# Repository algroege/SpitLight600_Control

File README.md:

// UART Communication 
// Frame Layout:
// <(SingleShot),(Shot),(PumpDelay),(PulseDivider),(DoublePulseDelay),(HV1),(HV2)>
// Example:
// <0,0,215,20,150,4.5,4.5>

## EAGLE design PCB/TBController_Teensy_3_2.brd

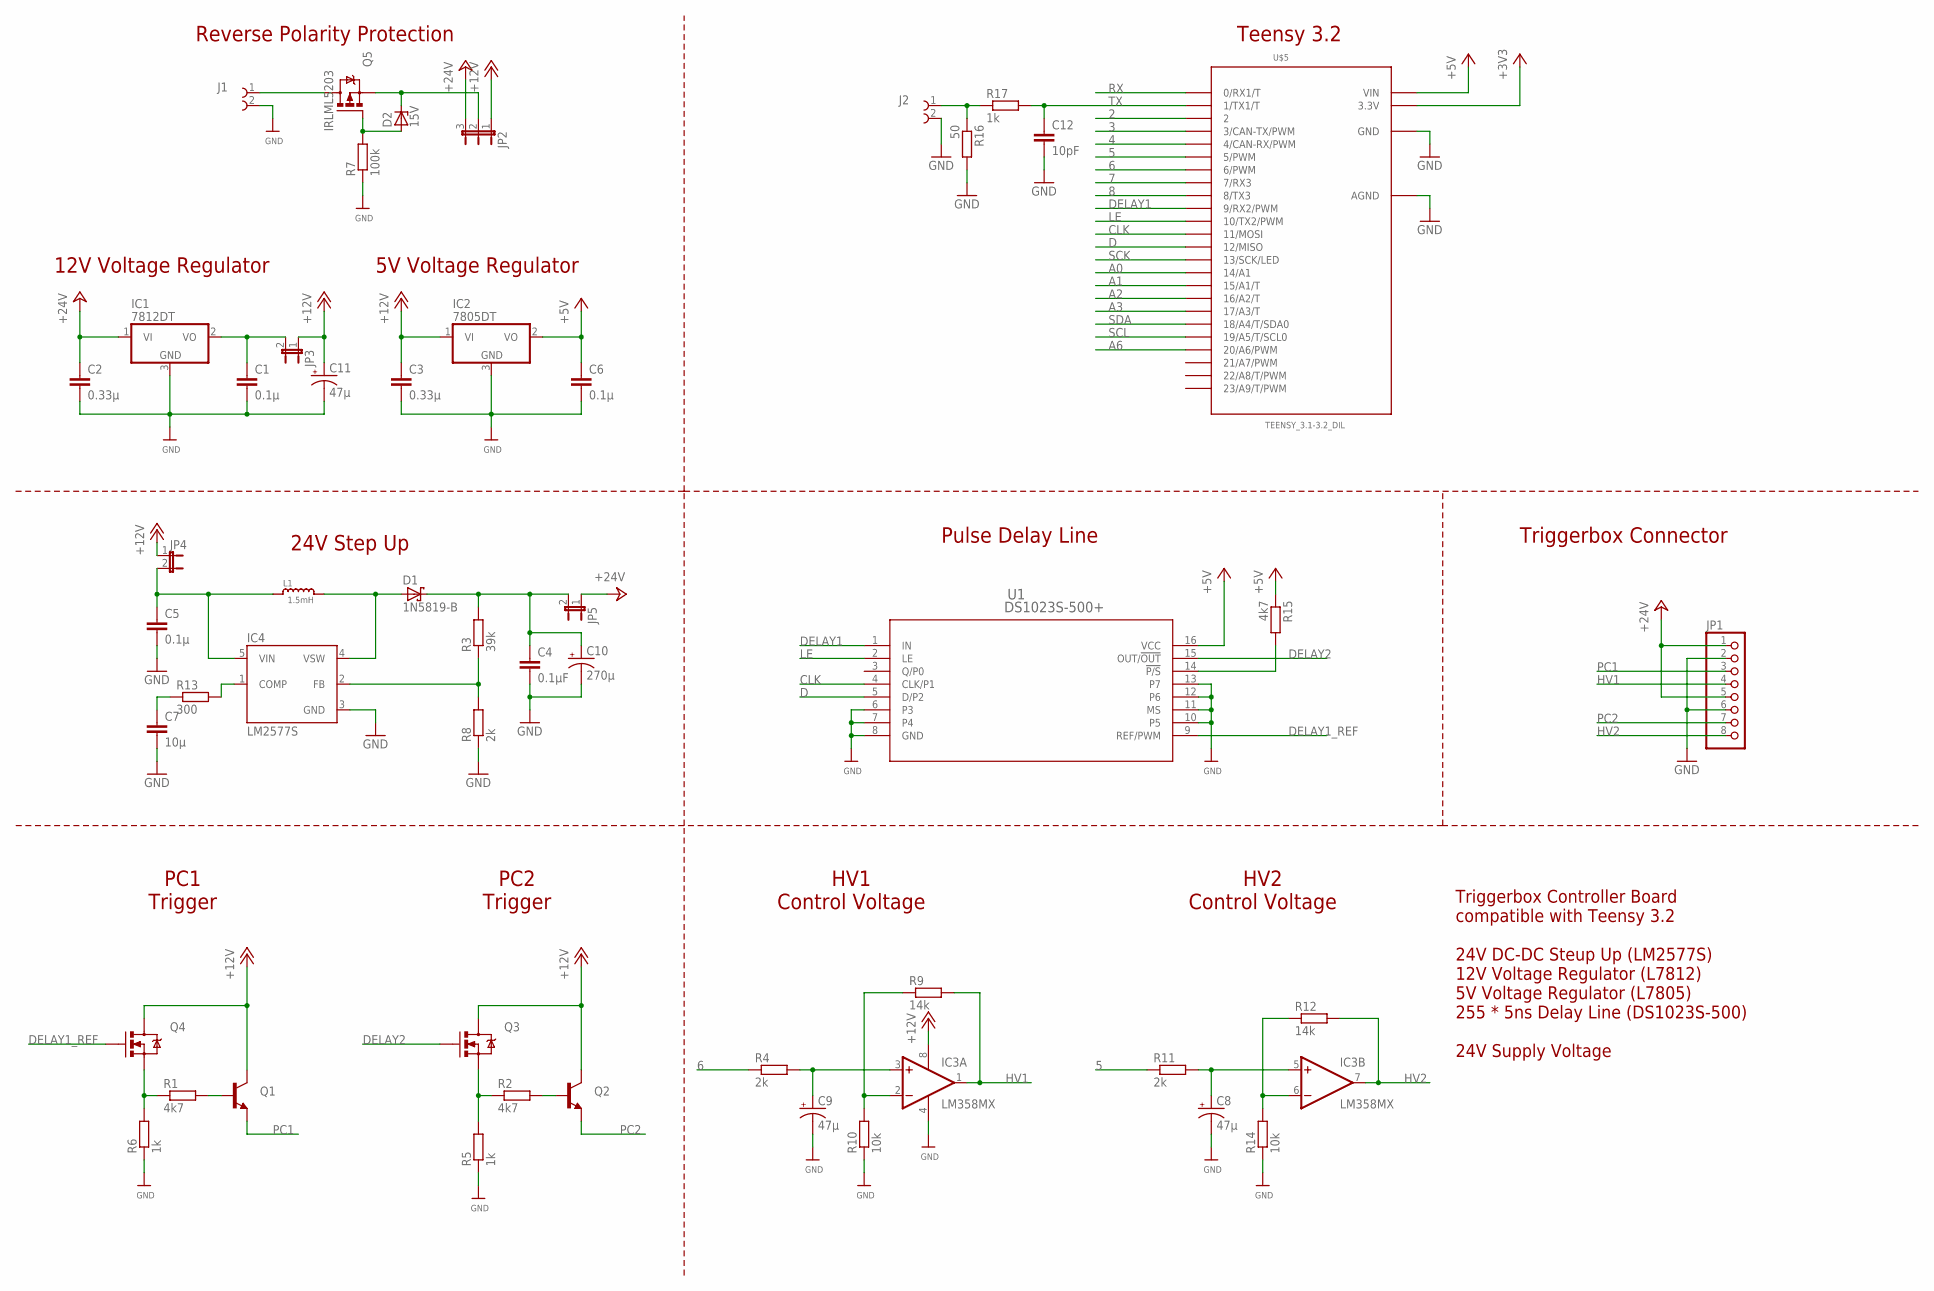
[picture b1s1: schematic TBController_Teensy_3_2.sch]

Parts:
C1, C5, C6: 0.1µ; C0805K
C2, C3: 0.33µ; C0805K
C4: 0.1µF; C0805K
C7: 10µ; C0805K
C8, C9, C11: 47µ; CPOL-RADIAL-100UF-25V
C10: 270µ; CPOL-RADIAL-100UF-25V
C12: 10pF; C0805K
D1: 1N5819-B; DO41-7.6
D2: 15V; SOT23
IC1: 7812DT; TO252
IC2: 7805DT; TO252
IC3: LM358MX; SO08
IC4: LM2577S; TO263-5
J1, J2: 691103110002
JP1: PINHD-1X8; 1X08
JP2: JP2E; JP2
JP3, JP4, JP5: JUMPER-2PTH_LOCK; 1X02_LOCK
L1: 1.5mH; WUERTH_WE_PD
Q1, Q2: TRANSISTOR_NPNSOT23; SOT23
Q3, Q4: MOSFET-NCHANNELSMD; SOT23-3
Q5: IRLML5203; MICRO3
R1, R2, R15: 4k7; R0805
R3: 39k; R0805
R4, R8, R11: 2k; R0805
R5, R6, R17: 1k; R0805
R7: 100k; R0805
R9, R12: 14k; R0805
R10, R14: 10k; R0805
R13: 300; R0805
R16: 50; R0805
U1: DS1023S-500+; 21-0042B_16
U$5: TEENSY_3.1-3.2_DIL; TEENSY_3.0-3.2&LC_DIL

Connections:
2: U$5.2
3: U$5.3 (3/CAN-TX/PWM)
4: U$5.4 (4/CAN-RX/PWM)
5: R11.1, U$5.5 (5/PWM)
6: R4.1, U$5.6 (6/PWM)
7: U$5.7 (7/RX3)
8: U$5.8 (8/TX3)
+3V3: U$5.3.3V
+5V: C6.1, IC2.2 (VO), R15.1, U1.16 (VCC), U$5.VIN
+12V: C3.1, C11.1 (+), IC2.1 (VI), IC3.8 (V+), JP2.1, JP3.1, JP4.1, Q1.3 (C), Q2.3 (C), Q3.3 (D), Q4.3 (D)
+24V: C2.1, IC1.1 (VI), JP1.1, JP1.5, JP2.3, JP5.1
A0: U$5.14/A0 (14/A1)
A1: U$5.15/A1 (15/A1/T)
A2: U$5.16/A2 (16/A2/T)
A3: U$5.17/A3 (17/A3/T)
A6: U$5.20/A6 (20/A6/PWM)
CLK: U1.4 (CLK/P1), U$5.11 (11/MOSI)
D: U1.5 (D/P2), U$5.12 (12/MISO)
DELAY1: U1.1 (IN), U$5.9 (9/RX2/PWM)
DELAY1_REF: Q4.1 (G), U1.9 (REF/PWM)
DELAY2: Q3.1 (G), U1.15 (OUT/!OUT)
GND: C1.2, C2.2, C3.2, C4.2, C5.2, C6.2, C7.2, C8.2 (-), C9.2 (-), C10.2 (-), C11.2 (-), C12.2, IC1.3 (GND), IC2.3 (GND), IC3.4 (V-), IC4.3 (GND), J1.2, J2.2, JP1.2, JP1.6, R5.1, R6.1, R7.1, R8.1, R10.1, R14.1, R16.2, U1.6 (P3), U1.7 (P4), U1.8 (GND), U1.10 (P5), U1.11 (MS), U1.12 (P6), U1.13 (P7), U$5.AGND, U$5.GND
HV1: IC3.1 (OUT), JP1.4, R9.2
HV2: IC3.7 (OUT), JP1.8, R12.2
LE: U1.2 (LE), U$5.10 (10/TX2/PWM)
unnamed: Q3.2 (S), R2.1, R5.2
unnamed: C12.1, R17.2, U$5.1 (1/TX1/T)
unnamed: C9.1 (+), IC3.3 (+IN), R4.2
unnamed: J1.1, Q5.3 (D)
unnamed: D2.1 (A), Q5.1 (G), R7.2
unnamed: IC3.2 (-IN), R9.1, R10.2
unnamed: R15.2, U1.14 (!P/S)
unnamed: Q4.2 (S), R1.1, R6.2
unnamed: Q1.1 (B), R1.2
unnamed: Q2.1 (B), R2.2
unnamed: D1.A, IC4.4 (VSW), L1.2
unnamed: C7.1, R13.1
unnamed: IC4.1 (COMP), R13.2
unnamed: IC4.2 (FB), R3.1, R8.2
unnamed: D2.3 (C), JP2.2, Q5.2 (S)
unnamed: C8.1 (+), IC3.5 (+IN), R11.2
unnamed: IC3.6 (-IN), R12.1, R14.2
unnamed: C1.1, IC1.2 (VO), JP3.2
unnamed: C5.1, IC4.5 (VIN), JP4.2, L1.1
unnamed: C4.1, C10.1 (+), D1.C, JP5.2, R3.2
PC1: JP1.3, Q1.2 (E)
PC2: JP1.7, Q2.2 (E)
RX: U$5.0 (0/RX1/T)
SCK: U$5.13 (13/SCK/LED)
SCL: U$5.19/A5 (19/A5/T/SCL0)
SDA: U$5.18/A4 (18/A4/T/SDA0)
TX: J2.1, R16.1, R17.1

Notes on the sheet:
Pulse Delay Line
5V Voltage Regulator
Triggerbox Controller Board compatible with Teensy 3.2 24V DC-DC Steup Up (LM2577S) 12V Voltage Regulator (L7812) 5V Voltage Regulator (L7805) 255 * 5ns Delay Line (DS1023S-500) 24V Supply Voltage
HV1 Control Voltage
HV2 Control Voltage
PC1 Trigger
PC2 Trigger
Teensy 3.2
24V Step Up
Triggerbox Connector
12V Voltage Regulator
Reverse Polarity Protection

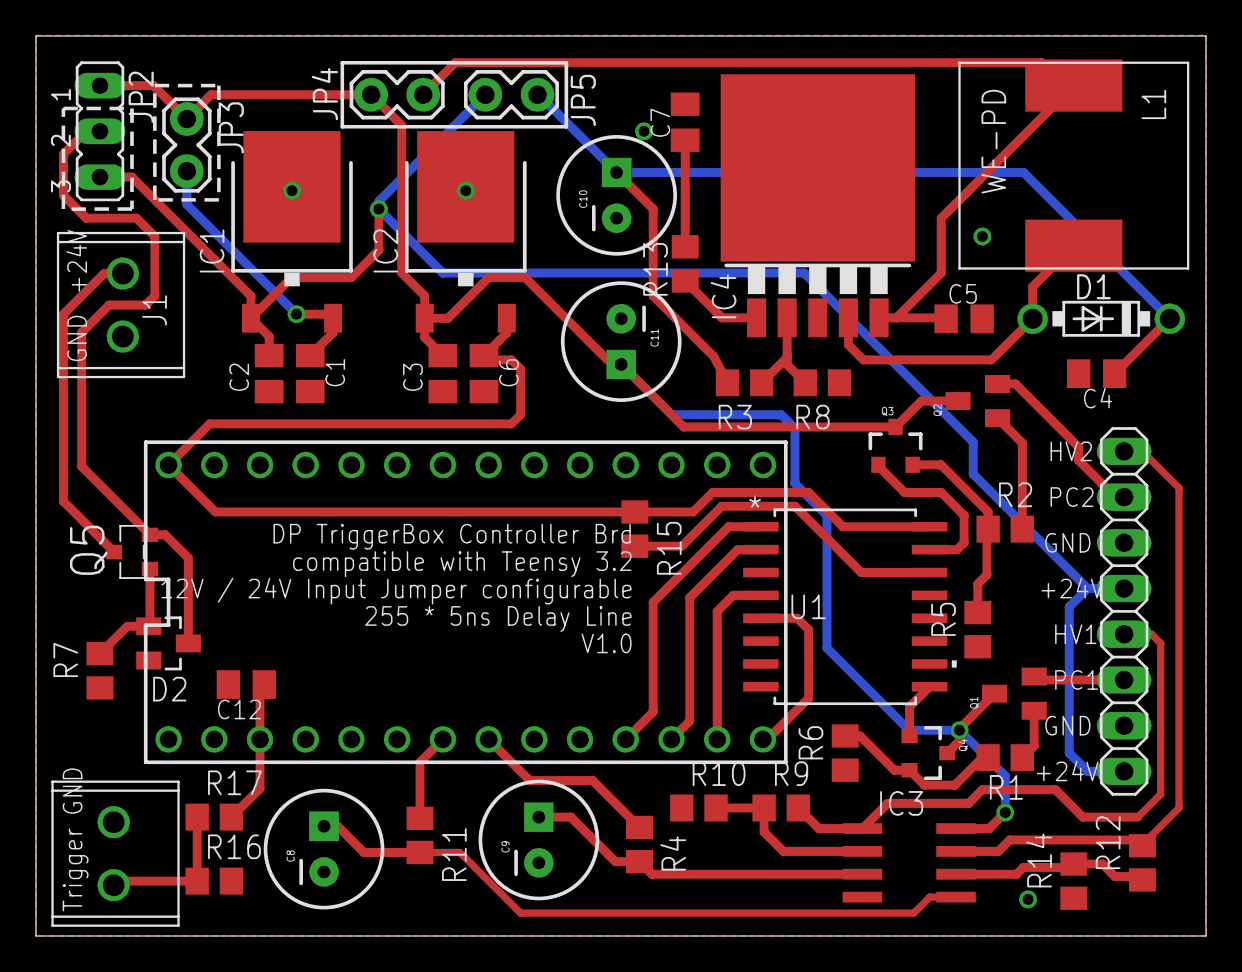
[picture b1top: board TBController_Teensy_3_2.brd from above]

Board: 2 copper layers, 65.0 x 50.0 mm, 50 parts (0 on the bottom side), 37 nets.

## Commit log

2024-05-04 Inital commit
2024-05-05 Create README.md
    Added
2024-05-07 changed C Label
2024-05-09 Changed Rep Rate Control
2024-05-09 Included PCB Files
2024-06-21 commented text to console output in sendFrame()

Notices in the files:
parts and their libraries:
EAGLE-TERMINAL_BLOCKS-rev16e: Copyright: Würth Elektronik
SparkFun: Licensing: CC v3.0 Share-Alike You are welcome to use this library for commercial purposes.
